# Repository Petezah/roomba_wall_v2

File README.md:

# roomba_wall_v2

An AVR device, based on ATTiny85, to transmit a virtual wall signal for an iRobot Roomba

## Folder layout

* /firmware
  * Source for the ATTiny85 firmware
* /hardware
  * Files describing the board layout, etc
* /christmas_tree_barrier
  * Files describing the board layout for the Christmas tree barrier variation

## Building

### Prerequisites for "happy path":

* Raspberry Pi configured with BCM SPI enabled
* AVR-GCC installed
  *  Easiest way to get this is 'sudo apt-get install arduino'
* Either:
  * A 6-position, dual-row IDC cable (recommended)
  * Or jumpers to wire SPI bus of Raspberry Pi to the ISP pads on the finished board

### Steps

#### hardware

* Order a board based on the files in https://github.com/Petezah/roomba_wall_v2/tree/master/hardware
  * Alternately, order one directly from OSH Park here: https://oshpark.com/shared_projects/yCviCn7Z
* Purchase parts from [Mouser electronics](http://mouser.com) using the current BOM
  * Use the ones with "mouser" in their filenames
* Assemble the board--parts are all marked on the silkscreen
  * NB: The ISP header should not be soldered to the board--merely insert the header pins into the IDC cable and wedge the pins into the vias during programming

#### firmware

There are two methods to wire the board for programming:

* *Recommended way*:
  *  Order my Raspberry Pi ISP board here: https://oshpark.com/shared_projects/iYtnPahC
  *  Assemble, and use an IDC cable as described above

* Alternate way: 
  * Hook up the ISP pins on the assembled board to your Raspberry PI as follows:
    * ISP Pin 1 --> Raspberry Pi Pin 21 (MISO)
    * ISP Pin 2 --> Raspberry Pi Pin 17 (3.3V)
    * ISP Pin 3 --> Raspberry Pi Pin 23 (SCK)
    * ISP Pin 4 --> Raspberry Pi Pin 19 (MOSI)
    * ISP Pin 5 --> Raspberry Pi Pin 15 (GPIO22)
    * ISP Pin 6 --> Raspberry Pi Pin 25 (GND)

Once wiring is accomplished:
* Execute the following on the Raspberry Pi command line
  * cd firmware
  * make fuse
  * make install

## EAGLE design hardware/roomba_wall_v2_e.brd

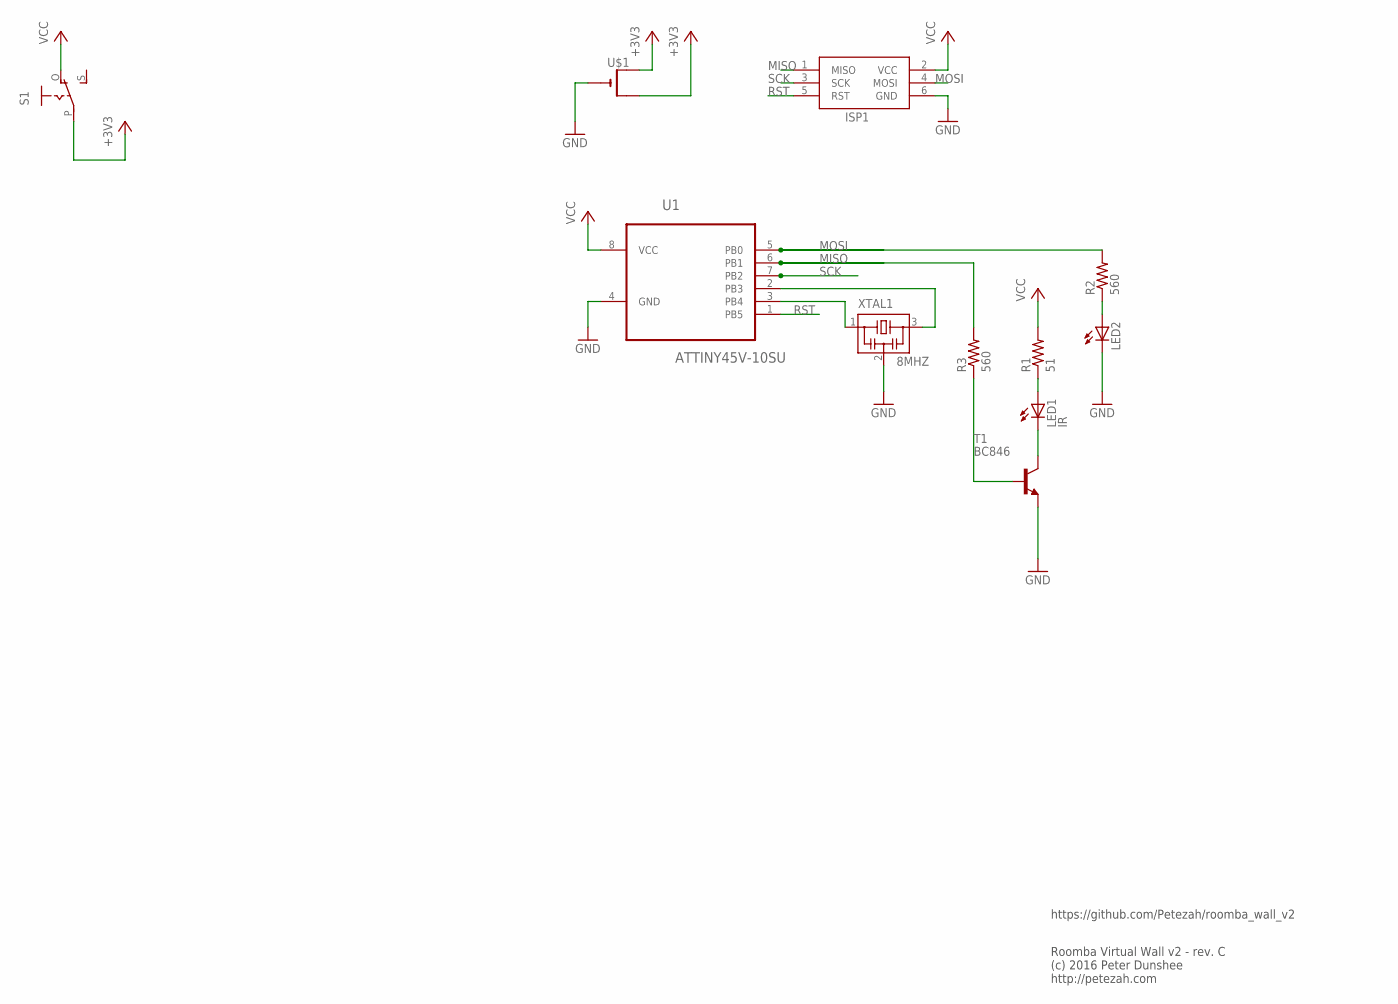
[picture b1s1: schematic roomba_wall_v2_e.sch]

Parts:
ISP1: AVRISP-6; AVRISP
LED1: IR; CHIPLED_0603
LED2: LEDCHIPLED_1206; CHIPLED_1206
R1: 51; R1206
R2, R3: 560; R1206
S1: EG1218S; EG1218
T1: BC846; SOT23
U1: ATTINY45V-10SU; SOIC127P798X216-8N
U$1: CR2032THM; CR2032-THRU
XTAL1: 8MHZ; CSTCR6M

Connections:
+3V3: S1.P, U$1.+1 (+), U$1.+2 (+1)
GND: ISP1.6 (GND), LED2.C, T1.2 (E), U1.4 (GND), U$1.-, XTAL1.2
MISO: ISP1.1 (MISO), R3.2, U1.6 (PB1)
MOSI: ISP1.4 (MOSI), R2.2, U1.5 (PB0)
unnamed: U1.3 (PB4), XTAL1.1
unnamed: U1.2 (PB3), XTAL1.3
unnamed: LED1.A, R1.1
unnamed: LED1.C, T1.3 (C)
unnamed: R3.1, T1.1 (B)
unnamed: LED2.A, R2.1
RST: ISP1.5 (RST), U1.1 (PB5)
SCK: ISP1.3 (SCK), U1.7 (PB2)
VCC: ISP1.2 (VCC), R1.2, S1.O, U1.8 (VCC)

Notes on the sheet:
Roomba Virtual Wall v2 - rev. C (c) 2016 Peter Dunshee http://petezah.com
https://github.com/Petezah/roomba_wall_v2

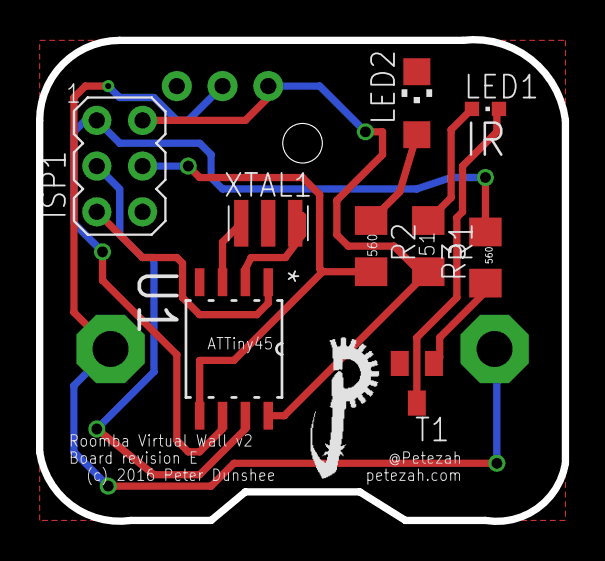
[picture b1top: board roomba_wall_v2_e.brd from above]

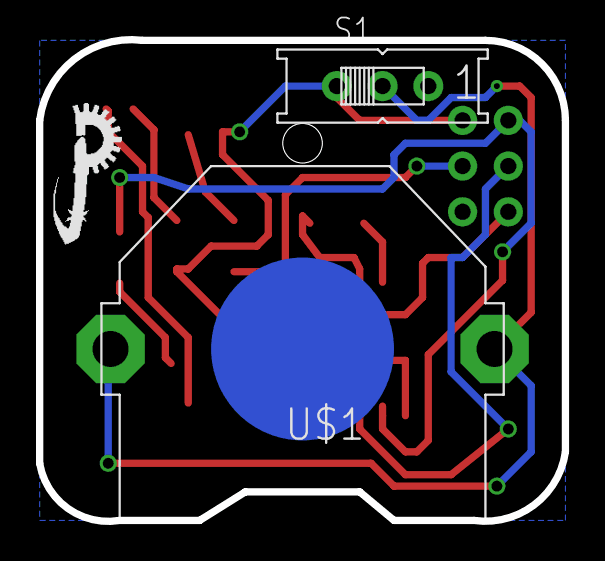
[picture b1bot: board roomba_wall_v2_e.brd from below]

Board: 2 copper layers, 29.2 x 26.8 mm, 13 parts (3 on the bottom side), 13 nets.

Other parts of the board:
U$2, U$3: LOGO_TINY

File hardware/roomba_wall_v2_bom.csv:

"Part";"Value";"Device";"Package";"Description";"MPN";"OC_FARNELL";"OC_NEWARK";"PACKAGE";"SUPPLIER";"VALUE";
"CN1";"";"DCBARRELPTH";"DCJACK_2MM_PTH";"2.0mm DC Barrel Jack";"";"";"";"";"";"";
"CN2";"";"JST_2PIN-SMT-RA";"JST-PH-2-SMT-RA";"JST 2-Pin Connectors of various flavors";"";"";"";"";"";"";
"IC1";"ATTINY85-20PU";"ATTINY85-20PU";"DIP254P762X533-8";"8-bit Microcontroller with In-System Programmable Flash";"ATTINY85-20PU";"1455162";"58M3796";"PDIP-8";"Atmel";"";
"ISP1";"AVRISP-6";"AVRISP-6";"AVRISP";"AVR ISP HEADER";"";"";"";"";"";"";
"LED1";"IR";"LED3MM";"LED3MM";"LED";"";"";"";"";"";"";
"LED2";"";"LED3MM";"LED3MM";"LED";"";"";"";"";"";"";
"R1";"51";"R-US_0204/7";"0204/7";"RESISTOR, American symbol";"";"";"";"";"";"";
"R2";"560";"R-US_0204/7";"0204/7";"RESISTOR, American symbol";"";"";"";"";"";"";
"R3";"560";"R-US_0204/7";"0204/7";"RESISTOR, American symbol";"";"";"";"";"";"";
"S1";"";"EG1218S";"EG1218";"SLIDING SWITCH";"";"";"";"";"";"";
"T1";"2N2222";"2N2222";"TO92-EBC-OVAL";"NPN TRANSISTOR";"";"";"";"";"";"";
"U$1";"";"CR2032THM";"CR2032-THRU";"";"";"";"";"";"";"";
"XTAL1";"8MHZ";"DIP-CERAMIC-RESONATOR/-OSCILLATOR-8MHZ(3P-2.5-8X3MM)";"X3-2.5-8X3X5.5MM";"306030010";"CSTLS8M00G53Z-A0";"";"";"";"";"8MHZ";

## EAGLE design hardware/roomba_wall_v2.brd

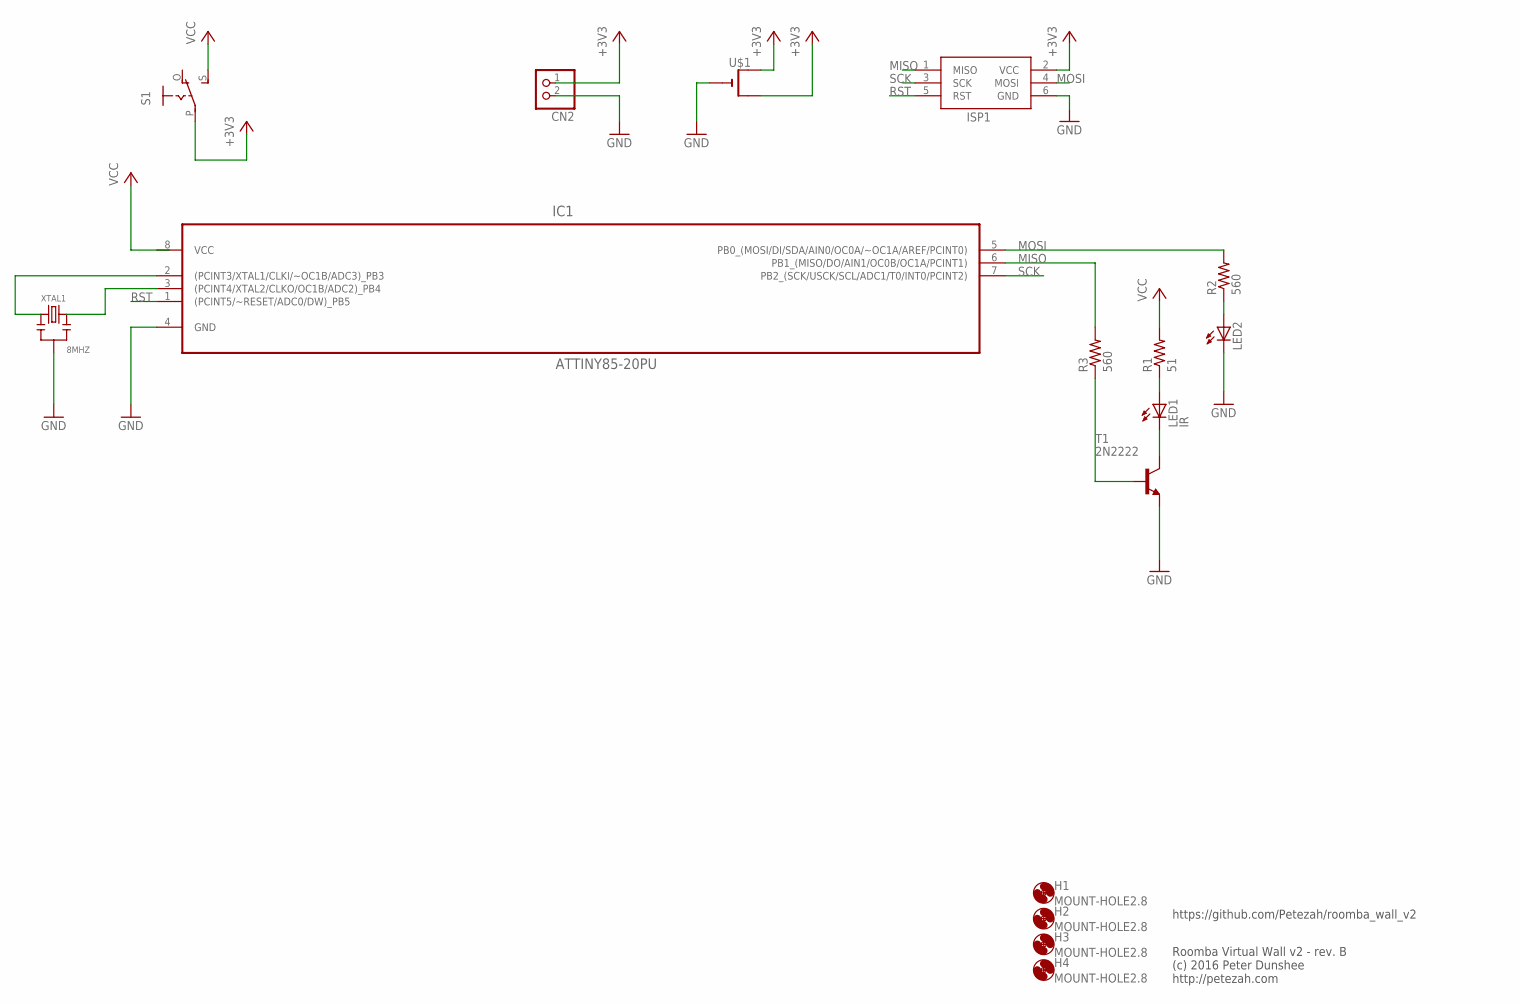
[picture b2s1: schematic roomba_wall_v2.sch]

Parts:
CN2: JST_2PIN-SMT-RA; JST-PH-2-SMT-RA
H1, H2, H3, H4: MOUNT-HOLE2.8; 2,8
IC1: ATTINY85-20PU; DIP254P762X533-8
ISP1: AVRISP-6; AVRISP
LED1: IR; LED3MM
LED2: LED3MM
R1: 51; 0204/7
R2, R3: 560; 0204/7
S1: EG1218S; EG1218
T1: 2N2222; TO92-EBC-OVAL
U$1: CR2032THM; CR2032-THRU
XTAL1: 8MHZ; X3-2.5-8X3X5.5MM

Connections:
+3V3: CN2.1 (2), ISP1.2 (VCC), S1.P, U$1.+1 (+), U$1.+2 (+1)
GND: CN2.2 (1), IC1.4 (GND), ISP1.6 (GND), LED2.K (C), T1.E, U$1.-, XTAL1.2
MISO: IC1.6 (PB1_(MISO/DO/AIN1/OC0B/OC1A/PCINT1)), ISP1.1 (MISO), R3.2
MOSI: IC1.5 (PB0_(MOSI/DI/SDA/AIN0/OC0A/~OC1A/AREF/P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), ISP1.4 (MOSI), R2.2
unnamed: IC1.2 ((PCINT3/XTAL1/CLKI/~OC1B/ADC3)_PB3), XTAL1.1
unnamed: IC1.3 ((PCINT4/XTAL2/CLKO/OC1B/ADC2)_PB4), XTAL1.3
unnamed: LED1.A, R1.1
unnamed: LED1.K (C), T1.C
unnamed: R3.1, T1.B
unnamed: LED2.A, R2.1
RST: IC1.1 ((PCINT5/~RESET/ADC0/DW)_PB5), ISP1.5 (RST)
SCK: IC1.7 (PB2_(SCK/USCK/SCL/ADC1/T0/INT0/PCINT2)), ISP1.3 (SCK)
VCC: IC1.8 (VCC), R1.2, S1.S

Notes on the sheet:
Roomba Virtual Wall v2 - rev. B (c) 2016 Peter Dunshee http://petezah.com
https://github.com/Petezah/roomba_wall_v2

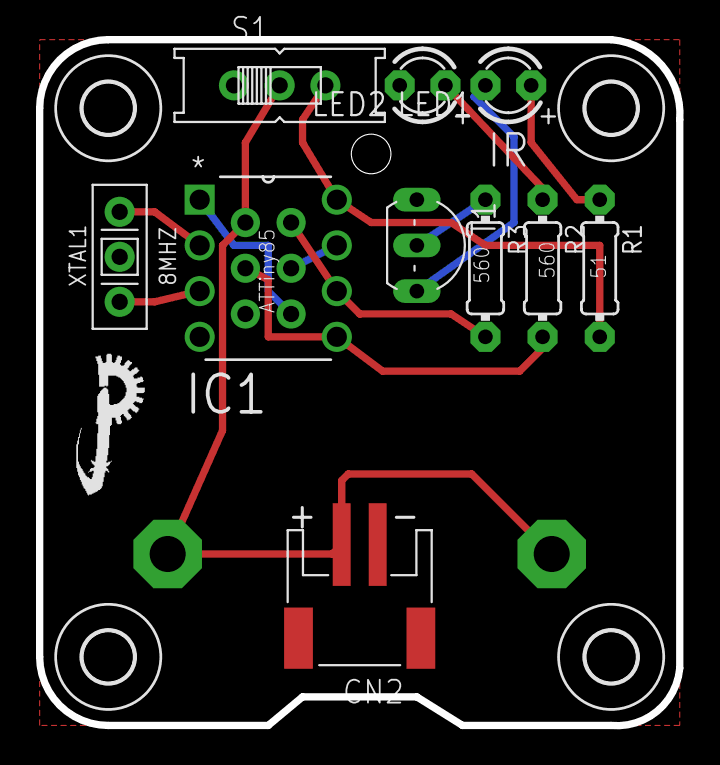
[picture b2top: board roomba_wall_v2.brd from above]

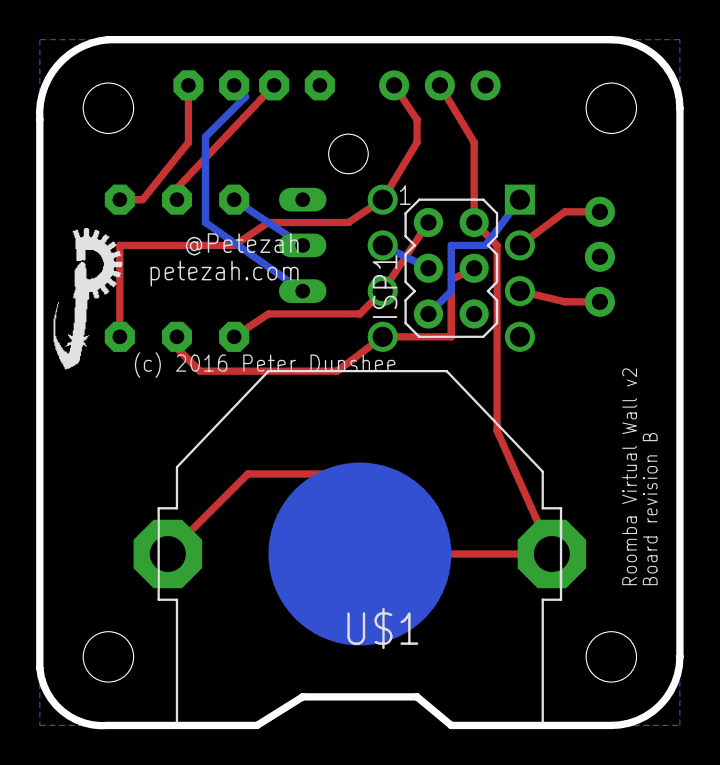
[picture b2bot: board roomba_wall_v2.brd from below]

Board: 2 copper layers, 35.6 x 38.1 mm, 18 parts (3 on the bottom side), 13 nets.

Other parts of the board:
U$2, U$3: LOGO_TINY

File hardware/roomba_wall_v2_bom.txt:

roomba_wall_v2 rev. A
--------------------------------------------------------------
Part  Value         Device                                               Package          Description                                             MPN              OC_FARNELL OC_NEWARK PACKAGE SUPPLIER VALUE
CN1                 DCBARRELPTH                                          DCJACK_2MM_PTH   2.0mm DC Barrel Jack                                                                                                
CN2                 JST_2PIN-SMT-RA                                      JST-PH-2-SMT-RA  JST 2-Pin Connectors of various flavors                                                                             
IC1   ATTINY85-20PU ATTINY85-20PU                                        DIP254P762X533-8 8-bit Microcontroller with In-System Programmable Flash ATTINY85-20PU    1455162    58M3796   PDIP-8  Atmel         
ISP1  AVRISP-6      AVRISP-6                                             AVRISP           AVR ISP HEADER                                                                                                      
LED1  IR            LED3MM                                               LED3MM           LED                                                                                                                 
LED2                LED3MM                                               LED3MM           LED                                                                                                                 
R1    51            R-US_0204/7                                          0204/7           RESISTOR, American symbol                                                                                           
R2    560           R-US_0204/7                                          0204/7           RESISTOR, American symbol                                                                                           
R3    560           R-US_0204/7                                          0204/7           RESISTOR, American symbol                                                                                           
S1                  EG1218S                                              EG1218           SLIDING SWITCH                                                                                                      
T1    2N2222        2N2222                                               TO92-EBC-OVAL    NPN TRANSISTOR                                                                                                      
U$1                 CR2032THM                                            CR2032-THRU                                                                                                                          
XTAL1 8MHZ          DIP-CERAMIC-RESONATOR/-OSCILLATOR-8MHZ(3P-2.5-8X3MM) X3-2.5-8X3X5.5MM 306030010                                               CSTLS8M00G53Z-A0                                       8MHZ

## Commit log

2016-05-12 Starting with v1 of the roomba wall project
2016-05-12 Reworked project for bare ATTiny85 * Moved 3rd party roomba send logic into its own file * Integrated just the portions of the IRRemote library that we need * Integrated our one Arduino dependency, w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
2016-05-13 Trying to switch our clock over to timer 1 to free up timer 0 exclusively for pwm
2016-05-13 Simplified by eliminating the clock timing required by the wiring delay functions and instead use a hand-tuned delay function specifically for 8Mhz ATTiny85 from the TV-B-Gone project. Also inspired 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
2016-05-15 Made a layout image of the prototype for reference. Moved hardware and firmware files into separate directories.
2016-05-16 Update README.md
    Added build steps, etc.
2016-05-18 Rev A of schematic and pcb layout
2016-05-18 BOM in CSV format
2016-05-23 Exported more useful BOM from Mouser
2016-06-05 Photo of the finished product
2016-06-05 Update readme with current instructions
2016-06-05 Fixed image link
2016-06-15 Doubled the IR transmit delay This is an experiment, attempting to extend the battery life of the device.
2016-06-15 Changed the timing to improve battery life again It now transmits once per second instead of once per .02 seconds. Testing the firmware with the device, it still stops the roomba. Battery life should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
2016-08-22 PCB layout, rev B 1/3 smaller, with mounting holes and cutout for the battery holder
2016-08-22 Update schematic printout
2016-09-04 Rev C and D boards C: ATTiny85/45 in SOIC package D: ATTiny45 in TSSOP package
2016-09-10 Reorganize project and update BOM
2016-09-10 Updated the readme
2016-09-21 Fixed some bits that never got updated Some instructions changed with Rev B; I missed some steps in prerequisites
2016-09-21 Updated image with picture of rev B board
2016-10-30 Rev E board SOIC ATTiny 1206 indicator LED 0603 IR LED
    Larger uC to make assembly easier than the SSOP. SMD LEDs to make the board more durable to life in the hallway.
2017-11-26 Print out size during buildwq
2017-11-26 Latest changes to rev E Not sure what's in here; they were made a while ago and just weren't committed. This is possibly the fix to the unconnected GND on the MCU.
2017-11-26 Starting Christmas tree barrier project
2017-11-27 Finished new schematic; started pcb layout
2017-11-28 Working on new pcb
2017-11-28 Place parts nicely
2017-11-28 Mostly finalize placement and outline
2017-11-29 Finished layout and routing Also just a bit of silkscreen
2017-12-01 Archive symbols and footprints
2017-12-01 Ignore KiCAD backup files
2017-12-04 Fix transistor on schematic Accidentally had a PNP instead of an NPN; doesn't change the PCB layout, I just made the mistake on the schematic.
2018-01-03 Fix footprints SOIC-8 was wrong--body was too narrow and pads too short LEDs were unclear--cathode indicator was on top of solder mask area
    Also plotted gerbers
2018-02-21 Latest PCB work
2018-02-24 Tweaks for Christmas tree barrier
2018-02-24 Latest gerber plots
2020-12-12 Rev b of Christmas Tree Barrier
    SOIC footprint is now fixed (wider pads)
